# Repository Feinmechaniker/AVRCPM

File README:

Aeternum
CP/M - System auf Basis eines AVR

verwendetets System ZSDOS

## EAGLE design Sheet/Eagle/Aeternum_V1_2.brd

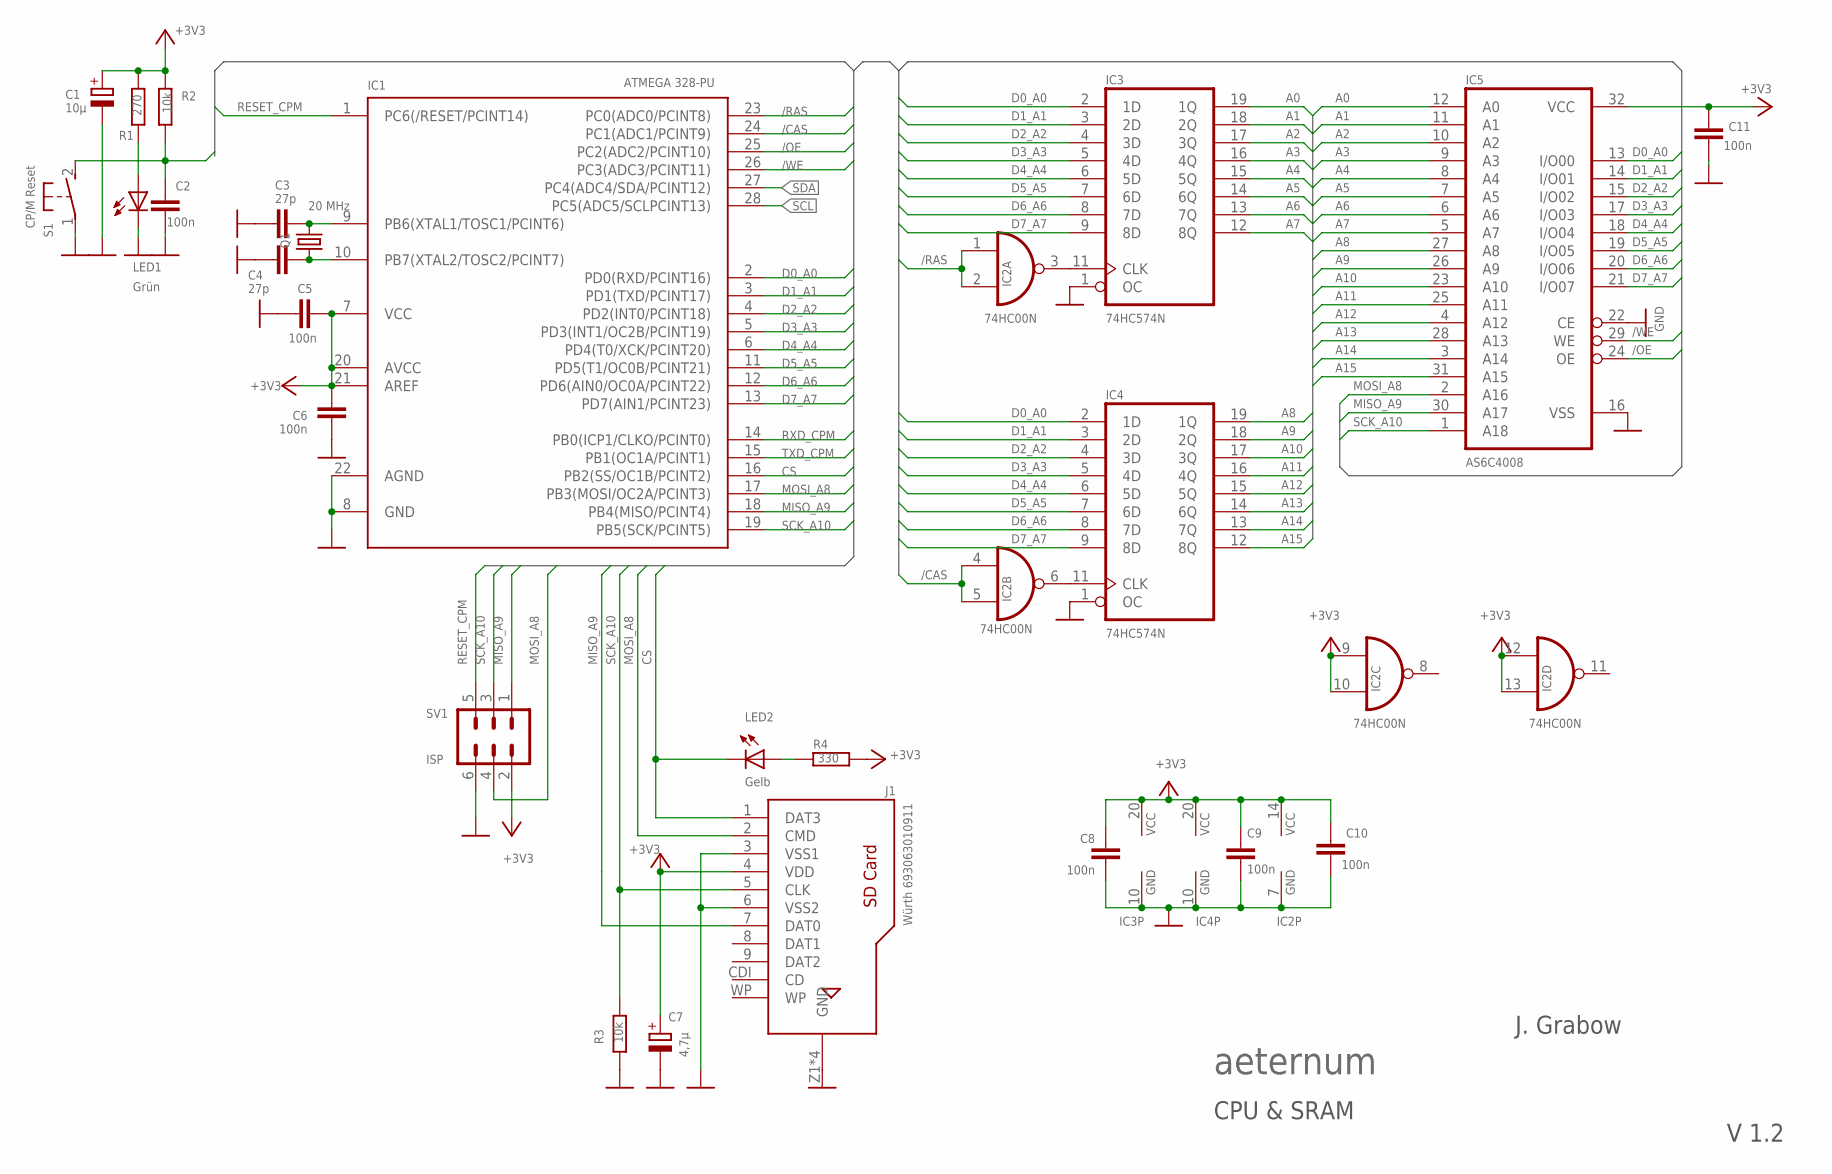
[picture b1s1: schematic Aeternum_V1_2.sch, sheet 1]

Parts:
C1: 10µ; E2-5
C2, C5, C6, C8, C9, C10, C11: 100n; C025-024X044
C3, C4: 27p; C025-024X044
C7: 4,7µ; E2-5
IC1: ATMEGA 328-PU; DIL28-3
IC2: 74HC00N; DIL14
IC3, IC4: 74HC574N; DIL20
IC5: AS6C4008; DIL32
J1: Würth 693063010911; 693063010911
LED1: Grün; CHIPLED_0603
LED2: Gelb; CHIPLED_0603
Q1: 20 MHz; HC49/S
R1: 270; 0204V
R2, R3: 10k; 0204V
R4: 330; 0204V
S1: CP/M Reset; B3F-31XX
SV1: ISP; ML6

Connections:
+3V3: C1.+, C5.1, C6.2, C7.+, C8.1, C9.1, C10.1, C11.1, IC1.7 (VCC), IC1.20 (AVCC), IC1.21 (AREF), IC2.9 (I0), IC2.10 (I1), IC2.12 (I0), IC2.13 (I1), IC2.14 (VCC), IC3.20 (VCC), IC4.20 (VCC), IC5.32 (VCC), J1.4 (VDD), R1.2, R2.1, R4.2, SV1.2; also elsewhere on the board
/CAS: IC1.24 (PC1(ADC1/PCINT9)), IC2.4 (I0), IC2.5 (I1)
/OE: IC1.25 (PC2(ADC2/PCINT10)), IC5.24 (OE)
/RAS: IC1.23 (PC0(ADC0/PCINT8)), IC2.1 (I0), IC2.2 (I1)
/WE: IC1.26 (PC3(ADC3/PCINT11)), IC5.29 (WE)
A0: IC3.19 (1Q), IC5.12 (A0)
A1: IC3.18 (2Q), IC5.11 (A1)
A2: IC3.17 (3Q), IC5.10 (A2)
A3: IC3.16 (4Q), IC5.9 (A3)
A4: IC3.15 (5Q), IC5.8 (A4)
A5: IC3.14 (6Q), IC5.7 (A5)
A6: IC3.13 (7Q), IC5.6 (A6)
A7: IC3.12 (8Q), IC5.5 (A7)
A8: IC4.19 (1Q), IC5.27 (A8)
A9: IC4.18 (2Q), IC5.26 (A9)
A10: IC4.17 (3Q), IC5.23 (A10)
A11: IC4.16 (4Q), IC5.25 (A11)
A12: IC4.15 (5Q), IC5.4 (A12)
A13: IC4.14 (6Q), IC5.28 (A13)
A14: IC4.13 (7Q), IC5.3 (A14)
A15: IC4.12 (8Q), IC5.31 (A15)
CS: IC1.16 (PB2(SS/OC1B/PCINT2)), J1.1 (DAT3), LED2.C
D0_A0: IC1.2 (PD0(RXD/PCINT16)), IC3.2 (1D), IC4.2 (1D), IC5.13 (I/O00)
D1_A1: IC1.3 (PD1(TXD/PCINT17)), IC3.3 (2D), IC4.3 (2D), IC5.14 (I/O01)
D2_A2: IC1.4 (PD2(INT0/PCINT18)), IC3.4 (3D), IC4.4 (3D), IC5.15 (I/O02)
D3_A3: IC1.5 (PD3(INT1/OC2B/PCINT19)), IC3.5 (4D), IC4.5 (4D), IC5.17 (I/O03)
D4_A4: IC1.6 (PD4(T0/XCK/PCINT20)), IC3.6 (5D), IC4.6 (5D), IC5.18 (I/O04)
D5_A5: IC1.11 (PD5(T1/OC0B/PCINT21)), IC3.7 (6D), IC4.7 (6D), IC5.19 (I/O05)
D6_A6: IC1.12 (PD6(AIN0/OC0A/PCINT22)), IC3.8 (7D), IC4.8 (7D), IC5.20 (I/O06)
D7_A7: IC1.13 (PD7(AIN1/PCINT23)), IC3.9 (8D), IC4.9 (8D), IC5.21 (I/O07)
GND: C1.-, C2.1, C3.2, C4.2, C5.2, C6.1, C7.-, C8.2, C9.2, C10.2, C11.2, IC1.8 (GND), IC1.22 (AGND), IC2.7 (GND), IC3.1 (OC), IC3.10 (GND), IC4.1 (OC), IC4.10 (GND), IC5.16 (VSS), IC5.22 (CE), J1.3 (VSS1), J1.6 (VSS2), J1.Z1 (GND), J1.Z2 (GND), J1.Z3 (GND), J1.Z4 (GND), LED1.C, R3.2, S1.1, SV1.6; also elsewhere on the board
MISO_A9: IC1.18 (PB4(MISO/PCINT4)), IC5.30 (A17), J1.7 (DAT0), SV1.1
MOSI_A8: IC1.17 (PB3(MOSI/OC2A/PCINT3)), IC5.2 (A16), J1.2 (CMD), SV1.4
unnamed: C4.1, IC1.10 (PB7(XTAL2/TOSC2/PCINT7)), Q1.1
unnamed: IC2.3 (O), IC3.11 (CLK)
unnamed: LED1.A, R1.1
unnamed: LED2.A, R4.1
unnamed: C3.1, IC1.9 (PB6(XTAL1/TOSC1/PCINT6)), Q1.2
unnamed: IC2.6 (O), IC4.11 (CLK)
RESET_CPM: C2.2, IC1.1 (PC6(/RESET/PCINT14)), R2.2, S1.2 (S), SV1.5; also elsewhere on the board
RXD_CPM: IC1.14 (PB0(ICP1/CLKO/PCINT0)); also elsewhere on the board
SCK_A10: IC1.19 (PB5(SCK/PCINT5)), IC5.1 (A18), J1.5 (CLK), R3.1, SV1.3
SCL: IC1.28 (PC5(ADC5/SCLPCINT13)); also elsewhere on the board
SDA: IC1.27 (PC4(ADC4/SDA/PCINT12)); also elsewhere on the board
TXD_CPM: IC1.15 (PB1(OC1A/PCINT1)); also elsewhere on the board

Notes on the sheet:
aeternum
V 1.2
J. Grabow
CPU & SRAM

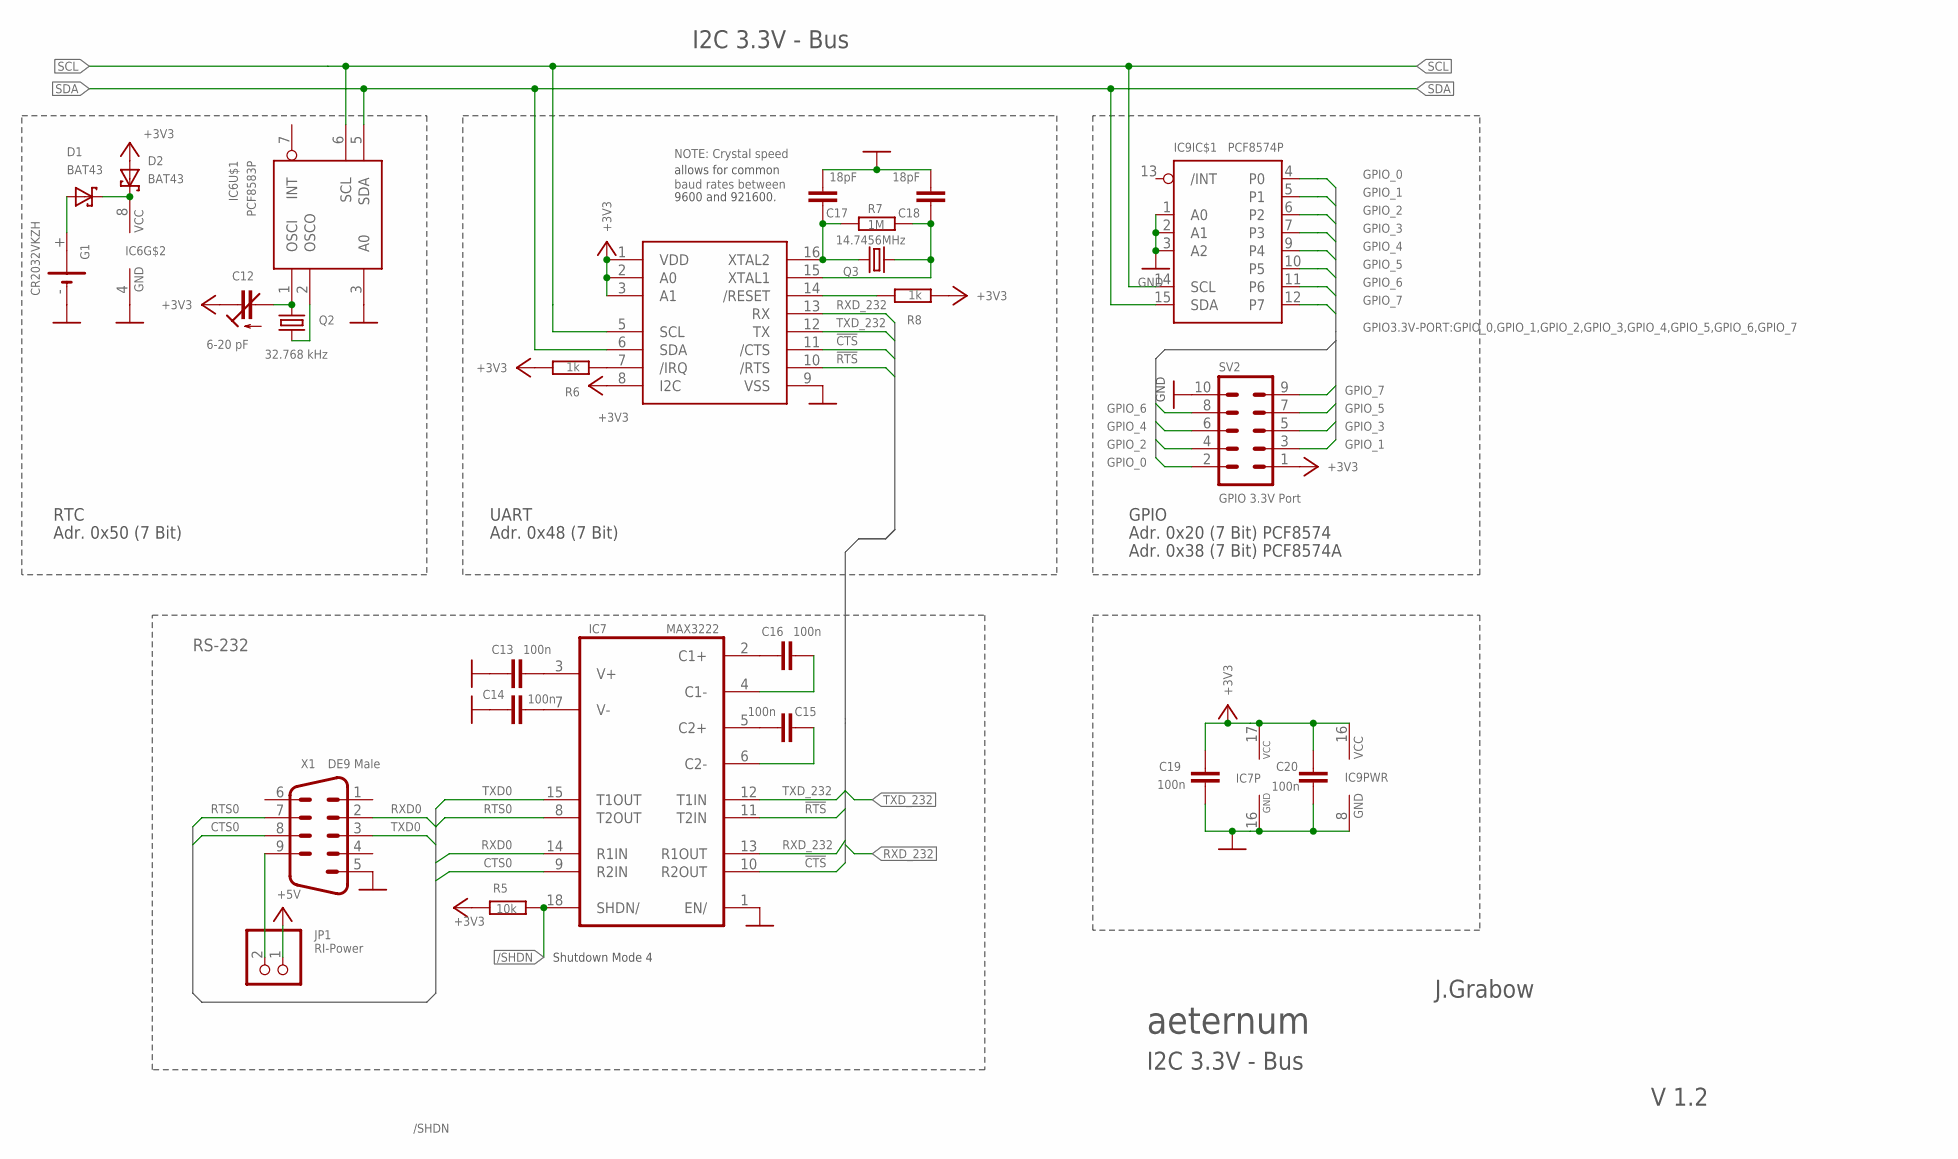
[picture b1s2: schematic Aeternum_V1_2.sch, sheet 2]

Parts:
C12: 6-20 pF; CTRIMTZ03
C13, C14, C15, C16, C19, C20: 100n; C025-024X044
C17, C18: 18pF; 0603-CAP
D1, D2: BAT43; E2LINE
G1: CR2032VKZH; KZH20PCB-V
IC6: PCF8583P; DIL08
IC7: MAX3222; DIL18
IC8: SC16IS740; RICKK2_SC16IS740
IC9: PCF8574P; DIL16
JP1: RI-Power; 1X02
Q2: 32.768 kHz; TC26H
Q3: 14.7456MHz; CRYSTAL-SMD-5X3
R5: 10k; 0204V
R6, R8: 1k; R0805
R7: 1M; R0805
SV2: GPIO 3.3V Port; ML10L
X1: DE9 Male; M09HP

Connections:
!CTS: IC7.10 (R2OUT), IC8.11 (/CTS)
!RTS: IC7.11 (T2IN), IC8.10 (/RTS)
+3V3: C12.1 (E), C19.2, C20.2, D2.2 (A), IC7.17 (VCC), IC8.1 (VDD), IC8.2 (A0), IC8.3 (A1), IC8.8 (I2C), IC9.16 (VCC), R5.2, R6.2, R8.1, SV2.1; also elsewhere on the board
+5V: JP1.1; also elsewhere on the board
/SHDN: IC7.18 (SHDN/), R5.1; also elsewhere on the board
CTS0: IC7.9 (R2IN), X1.8
GND: C13.2, C14.2, C17.2, C18.2, C19.1, C20.1, G1.-, IC6.3 (A0), IC6.4 (GND), IC7.1 (EN/), IC7.16 (GND), IC8.9 (VSS), IC9.1 (A0), IC9.2 (A1), IC9.3 (A2), IC9.8 (GND), SV2.10, X1.5; also elsewhere on the board
GPIO_0: IC9.4 (P0), SV2.2
GPIO_1: IC9.5 (P1), SV2.3
GPIO_2: IC9.6 (P2), SV2.4
GPIO_3: IC9.7 (P3), SV2.5
GPIO_4: IC9.9 (P4), SV2.6
GPIO_5: IC9.10 (P5), SV2.7
GPIO_6: IC9.11 (P6), SV2.8
GPIO_7: IC9.12 (P7), SV2.9
unnamed: C12.2 (A), IC6.1 (OSCI), Q2.1
unnamed: IC6.2 (OSCO), Q2.2
unnamed: C17.1, IC8.16 (XTAL2), Q3.3 (2), R7.1
unnamed: C16.2, IC7.2 (C1+)
unnamed: JP1.2, X1.9
unnamed: C15.1, IC7.5 (C2+)
unnamed: C14.1, IC7.7 (V-)
unnamed: C16.1, IC7.4 (C1-)
unnamed: C15.2, IC7.6 (C2-)
unnamed: C13.1, IC7.3 (V+)
unnamed: D1.1 (K), D2.1 (K), IC6.8 (VCC)
unnamed: D1.2 (A), G1.+
unnamed: C18.1, IC8.15 (XTAL1), Q3.1, R7.2
unnamed: IC8.14 (/RESET), R8.2
unnamed: IC8.7 (/IRQ), R6.1
RTS0: IC7.8 (T2OUT), X1.7
RXD0: IC7.14 (R1IN), X1.2
RXD_232: IC7.13 (R1OUT), IC8.13 (RX); also elsewhere on the board
SCL: IC6.6 (SCL), IC8.5 (SCL), IC9.14 (SCL); also elsewhere on the board
SDA: IC6.5 (SDA), IC8.6 (SDA), IC9.15 (SDA); also elsewhere on the board
TXD0: IC7.15 (T1OUT), X1.3
TXD_232: IC7.12 (T1IN), IC8.12 (TX); also elsewhere on the board

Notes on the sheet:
Adr. 0x50 (7 Bit)
RTC
NOTE: Crystal speed
baud rates between
UART
Adr. 0x48 (7 Bit)
allows for common
9600 and 921600.
GPIO
Adr. 0x20 (7 Bit) PCF8574
J.Grabow
V 1.2
I2C 3.3V - Bus
aeternum
RS-232
Shutdown Mode 4
Adr. 0x38 (7 Bit) PCF8574A

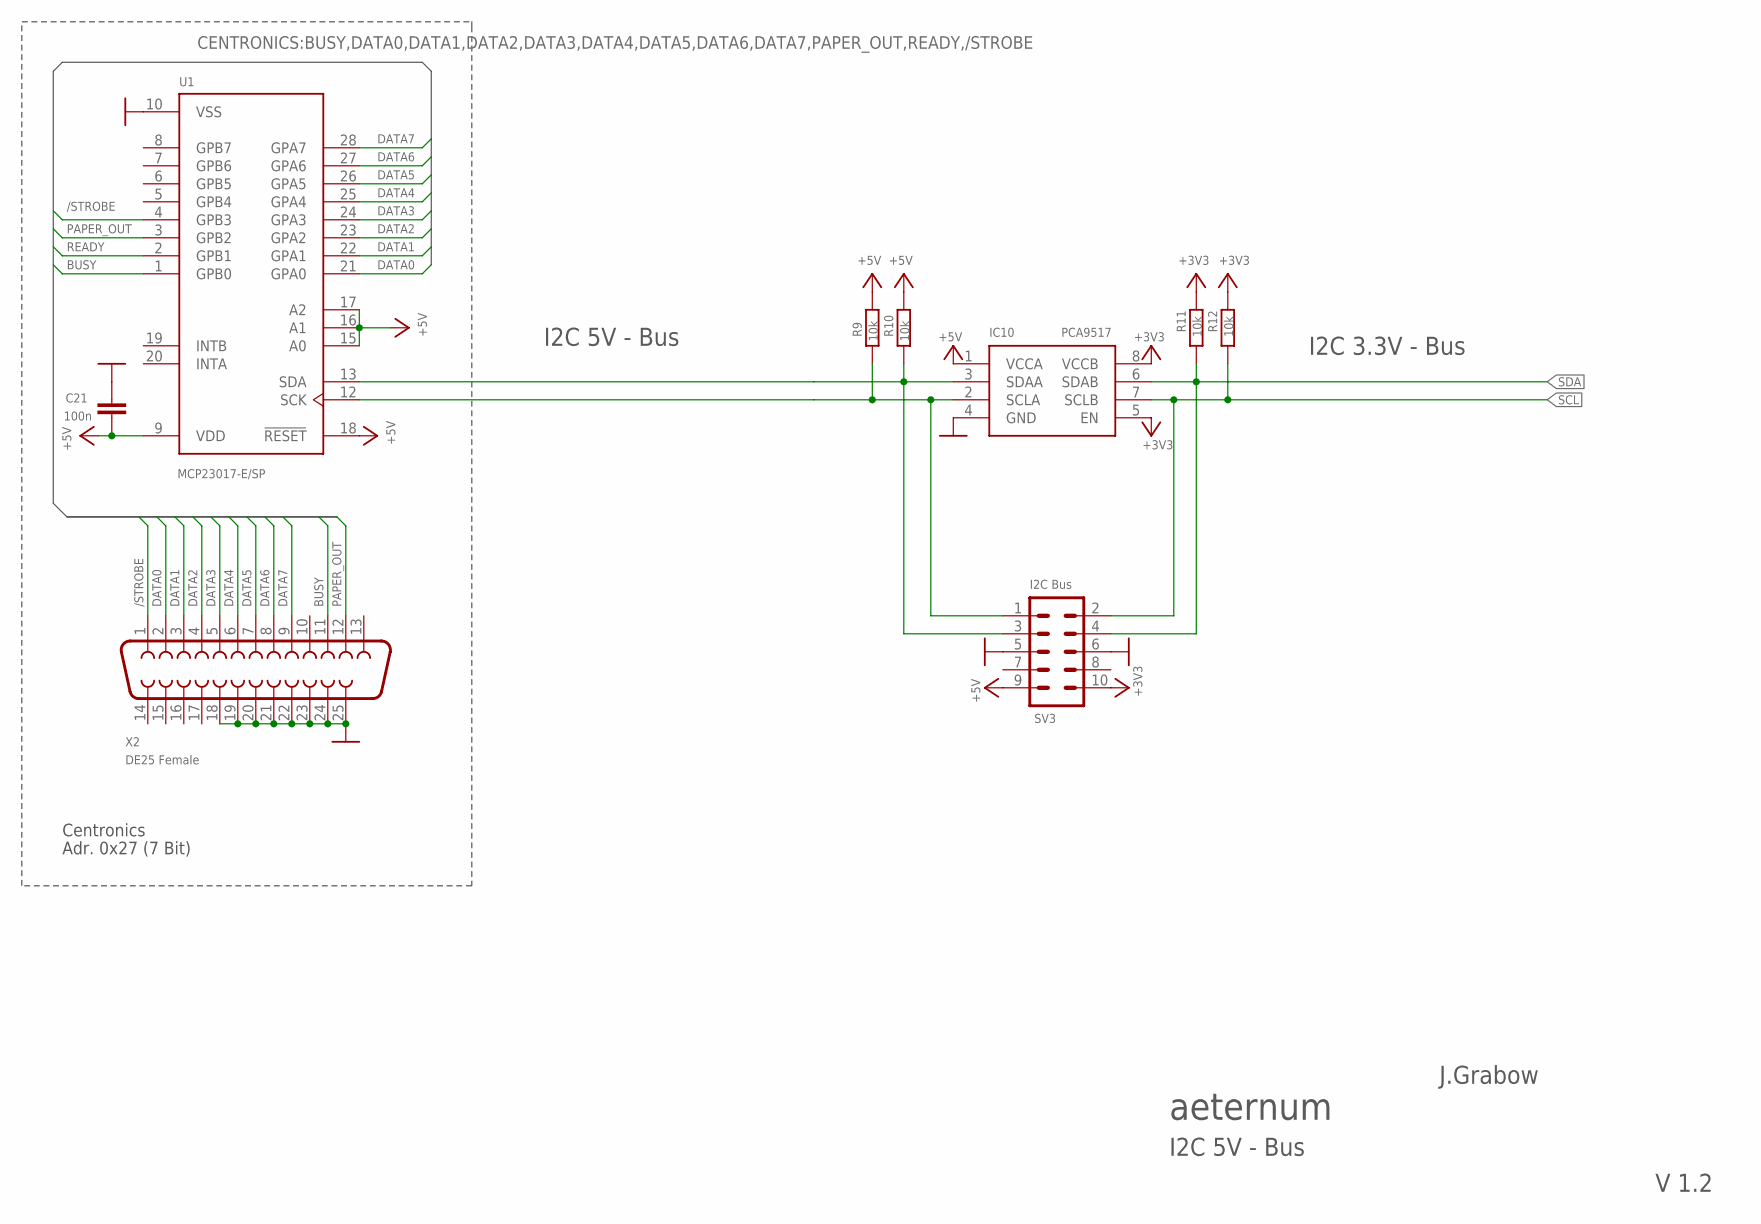
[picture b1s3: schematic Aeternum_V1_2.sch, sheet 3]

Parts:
C21: 100n; C025-024X044
IC10: PCA9517; SO-08
R9, R10, R11, R12: 10k; 0207/2V
SV3: I2C Bus; ML10L
U1: MCP23017-E/SP; DIP793W45P254L3556H508Q28
X2: DE25 Female; F25H

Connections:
+3V3: IC10.5 (EN), IC10.8 (VCCB), R11.2, R12.2, SV3.10; also elsewhere on the board
+5V: C21.1, IC10.1 (VCCA), R9.2, R10.2, SV3.9, U1.9 (VDD), U1.15 (A0), U1.16 (A1), U1.17 (A2), U1.18 (!RESET); also elsewhere on the board
/STROBE: U1.4 (GPB3), X2.1
BUSY: U1.1 (GPB0), X2.11
DATA0: U1.21 (GPA0), X2.2
DATA1: U1.22 (GPA1), X2.3
DATA2: U1.23 (GPA2), X2.4
DATA3: U1.24 (GPA3), X2.5
DATA4: U1.25 (GPA4), X2.6
DATA5: U1.26 (GPA5), X2.7
DATA6: U1.27 (GPA6), X2.8
DATA7: U1.28 (GPA7), X2.9
GND: C21.2, IC10.4 (GND), SV3.5, SV3.6, U1.10 (VSS), X2.18, X2.19, X2.20, X2.21, X2.22, X2.23, X2.24, X2.25; also elsewhere on the board
PAPER_OUT: U1.3 (GPB2), X2.12
READY: U1.2 (GPB1)
SCL: IC10.7 (SCLB), R12.1, SV3.2; also elsewhere on the board
SCLA: IC10.2 (SCLA), R9.1, SV3.1, U1.12 (SCK)
SDA: IC10.6 (SDAB), R11.1, SV3.4; also elsewhere on the board
SDAA: IC10.3 (SDAA), R10.1, SV3.3, U1.13 (SDA)

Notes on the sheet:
I2C 5V - Bus
aeternum
J.Grabow
V 1.2
I2C 3.3V - Bus
Adr. 0x27 (7 Bit)
Centronics

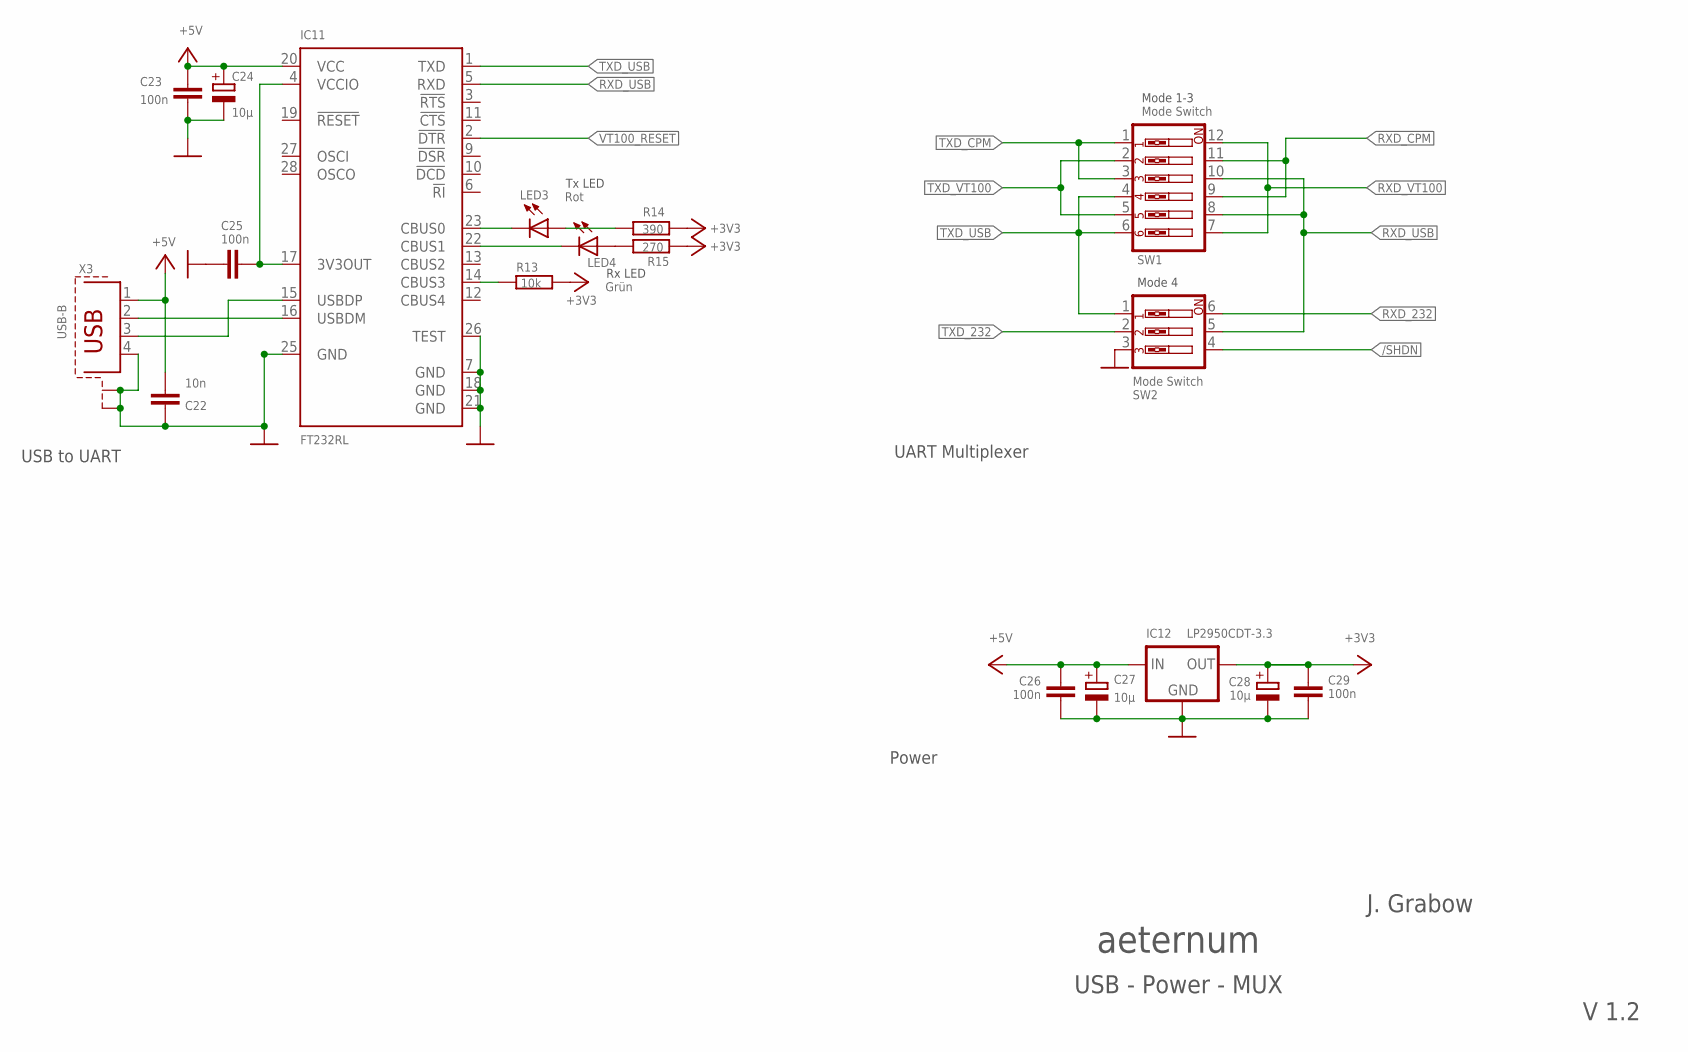
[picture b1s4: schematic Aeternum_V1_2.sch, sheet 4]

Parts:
C22: 10n; C025-024X044
C23, C25, C26, C29: 100n; C025-024X044
C24, C27, C28: 10µ; E2-5
IC11: FT232RL; SSOP28
IC12: LP2950CDT-3.3; DPACK
LED3: Rot; CHIPLED_0603
LED4: Grün; CHIPLED_0603
R13: 10k; 0204V
R14: 390; 0204V
R15: 270; 0204V
SW1: Mode Switch; EDG-06
SW2: Mode Switch; EDG-03
X3: USB-B; PN61729-S

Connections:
+3V3: C28.+, C29.2, IC12.3 (OUT), R13.2, R14.2, R15.2; also elsewhere on the board
+5V: C22.2, C23.2, C24.+, C26.2, C27.+, IC11.20 (VCC), IC12.1 (IN), X3.1; also elsewhere on the board
/SHDN: SW2.4; also elsewhere on the board
GND: C22.1, C23.1, C24.-, C25.1, C26.1, C27.-, C28.-, C29.1, IC11.7 (GND), IC11.18 (GND), IC11.21 (GND), IC11.25 (GND), IC11.26 (TEST), IC12.4 (GND), SW2.3, X3.4, X3.S1, X3.S2; also elsewhere on the board
unnamed: IC11.16 (USBDM), X3.2
unnamed: IC11.15 (USBDP), X3.3
unnamed: IC11.14 (CBUS3), R13.1
unnamed: C25.2, IC11.4 (VCCIO), IC11.17 (3V3OUT)
unnamed: IC11.23 (CBUS0), LED3.C
unnamed: IC11.22 (CBUS1), LED4.C
unnamed: LED4.A, R15.1
unnamed: LED3.A, R14.1
RXD_232: SW2.6; also elsewhere on the board
RXD_CPM: SW1.9, SW1.11; also elsewhere on the board
RXD_USB: IC11.5 (RXD), SW1.8, SW1.10, SW2.5
RXD_VT100: SW1.7, SW1.12; also elsewhere on the board
TXD_232: SW2.2; also elsewhere on the board
TXD_CPM: SW1.1, SW1.3; also elsewhere on the board
TXD_USB: IC11.1 (TXD), SW1.4, SW1.6, SW2.1
TXD_VT100: SW1.2, SW1.5; also elsewhere on the board
VT100_RESET: IC11.2 (!DTR); also elsewhere on the board

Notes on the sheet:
Mode 1-3
Mode 4
USB to UART
UART Multiplexer
Power
USB - Power - MUX
aeternum
J. Grabow
V 1.2
Tx LED
Rx LED

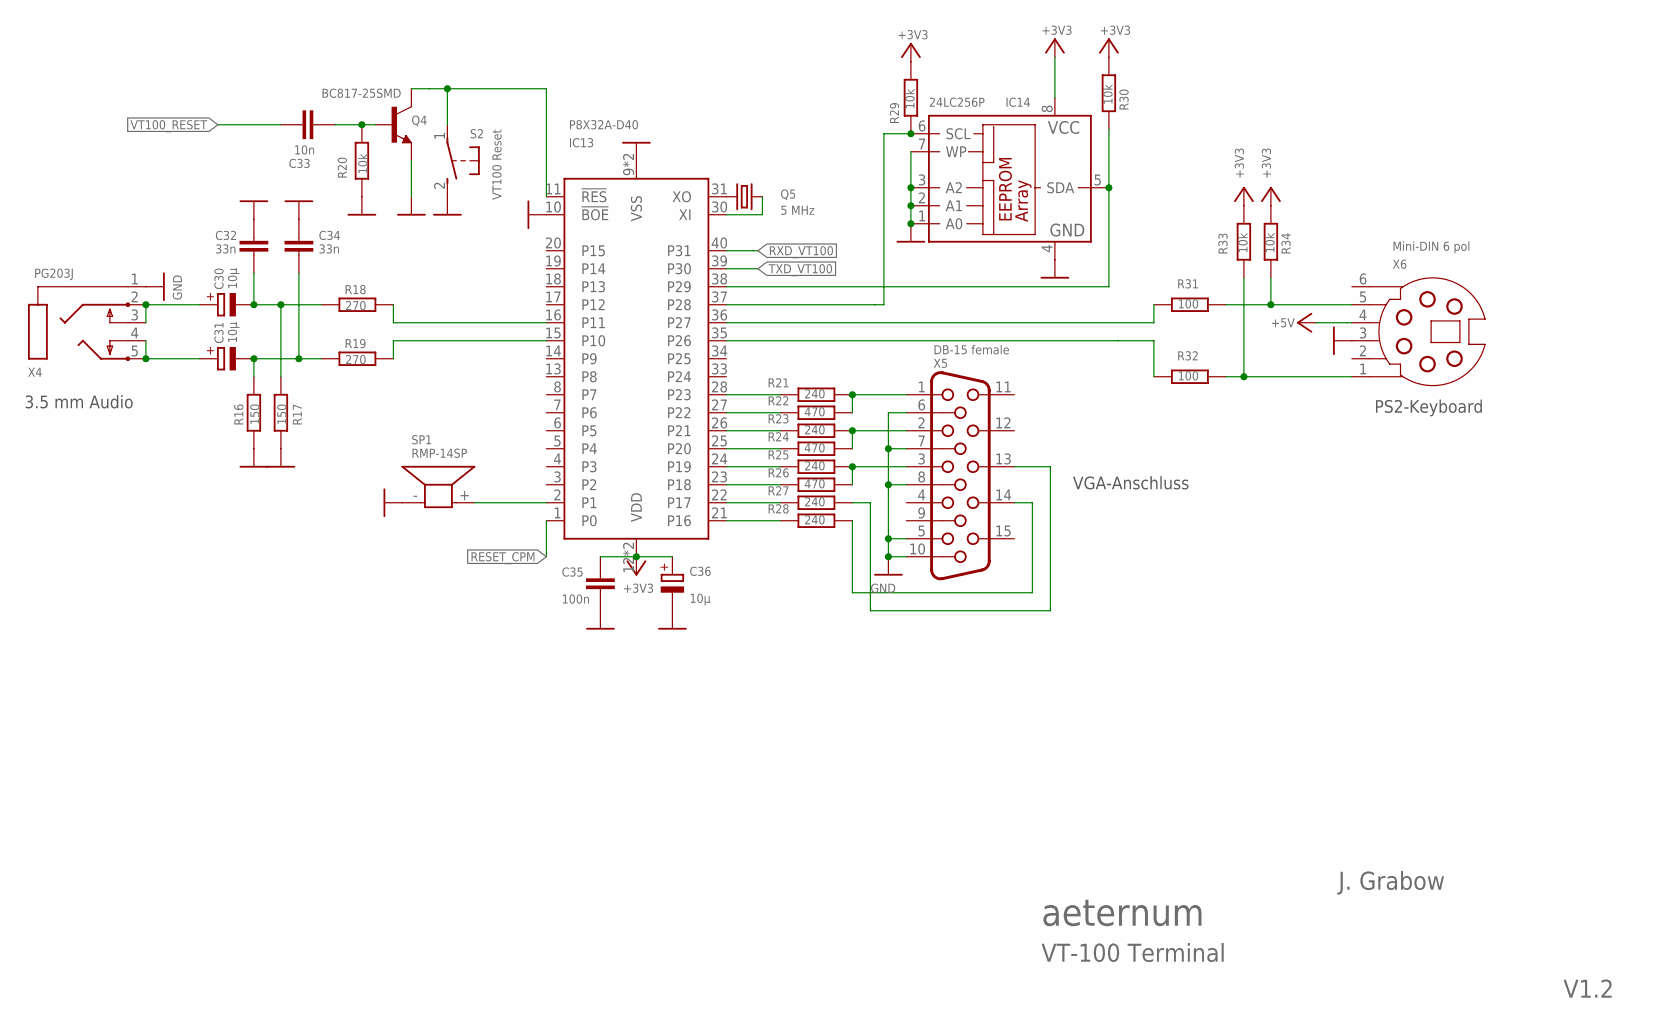
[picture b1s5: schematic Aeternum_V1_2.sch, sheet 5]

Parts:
C30, C31: 10µ; E2,5-5
C32, C34: 33n; C025-024X044
C33: 10n; C025-024X044
C35: 100n; C025-024X044
C36: 10µ; E2,5-6E
IC13: P8X32A-D40; DIL40
IC14: 24LC256P; DIL8
Q4: BC817-25SMD; SOT23-BEC
Q5: 5 MHz; HC49/S
R16, R17: 150; 0204V
R18, R19: 270; 0204V
R20, R33, R34: 10k; 0204V
R21, R23, R25, R27, R28: 240; 0204V
R22, R24, R26: 470; 0204V
R29, R30: 10k; 0204/7
R31, R32: 100; 0204V
S2: VT100 Reset; B3F-31XX
SP1: RMP-14SP; KSS1201
X4: PG203J
X5: DB-15 female; HDF15H
X6: Mini-DIN 6 pol; SSV-BC06

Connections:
+3V3: C35.2, C36.+, IC13.12 (VDD), IC13.32 (VDD), IC14.8 (VCC), R29.1, R30.1, R33.1, R34.1; also elsewhere on the board
+5V: X6.4; also elsewhere on the board
GND: C32.2, C34.2, C35.1, C36.-, IC13.9 (VSS), IC13.10 (!BOE), IC13.29 (VSS), IC14.1 (A0), IC14.2 (A1), IC14.3 (A2), IC14.4 (GND), IC14.7 (WP), Q4.E, R16.2, R17.2, R20.1, S2.2 (S), SP1.- (2), X4.1, X5.5, X5.6, X5.7, X5.8, X5.10, X6.3; also elsewhere on the board
unnamed: IC13.30 (XI), Q5.1
unnamed: R21.1, R22.1, X5.1
unnamed: IC13.28 (P23), R21.2
unnamed: IC13.27 (P22), R22.2
unnamed: R23.1, R24.1, X5.2
unnamed: IC13.26 (P21), R23.2
unnamed: IC13.25 (P20), R24.2
unnamed: R25.1, R26.1, X5.3
unnamed: IC13.24 (P19), R25.2
unnamed: IC13.23 (P18), R26.2
unnamed: IC13.22 (P17), R27.2
unnamed: IC13.21 (P16), R28.2
unnamed: R27.1, X5.13
unnamed: R28.1, X5.14
unnamed: R32.1, R33.2, X6.1
unnamed: R31.1, R34.2, X6.5
unnamed: IC13.31 (XO), Q5.2
unnamed: IC13.2 (P1), SP1.+ (1)
unnamed: C33.2, Q4.B, R20.2
unnamed: IC13.37 (P28), IC14.6 (SCL), R29.2
unnamed: IC13.38 (P29), IC14.5 (SDA), R30.2
unnamed: C31.-, C34.1, R16.1, R19.2
unnamed: C30.-, C32.1, R17.1, R18.2
unnamed: C30.+, X4.2, X4.3
unnamed: C31.+, X4.4, X4.5
P10: IC13.16 (P11), R18.1
P11: IC13.15 (P10), R19.1
P26: IC13.35 (P26), R32.2
P27: IC13.36 (P27), R31.2
PROP_RESET: IC13.11 (!RES), Q4.C, S2.1
RESET_CPM: IC13.1 (P0); also elsewhere on the board
RXD_VT100: IC13.40 (P31); also elsewhere on the board
TXD_VT100: IC13.39 (P30); also elsewhere on the board
VT100_RESET: C33.1; also elsewhere on the board

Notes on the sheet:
aeternum
J. Grabow
VT-100 Terminal
V1.2
PS2-Keyboard
VGA-Anschluss
3.5 mm Audio

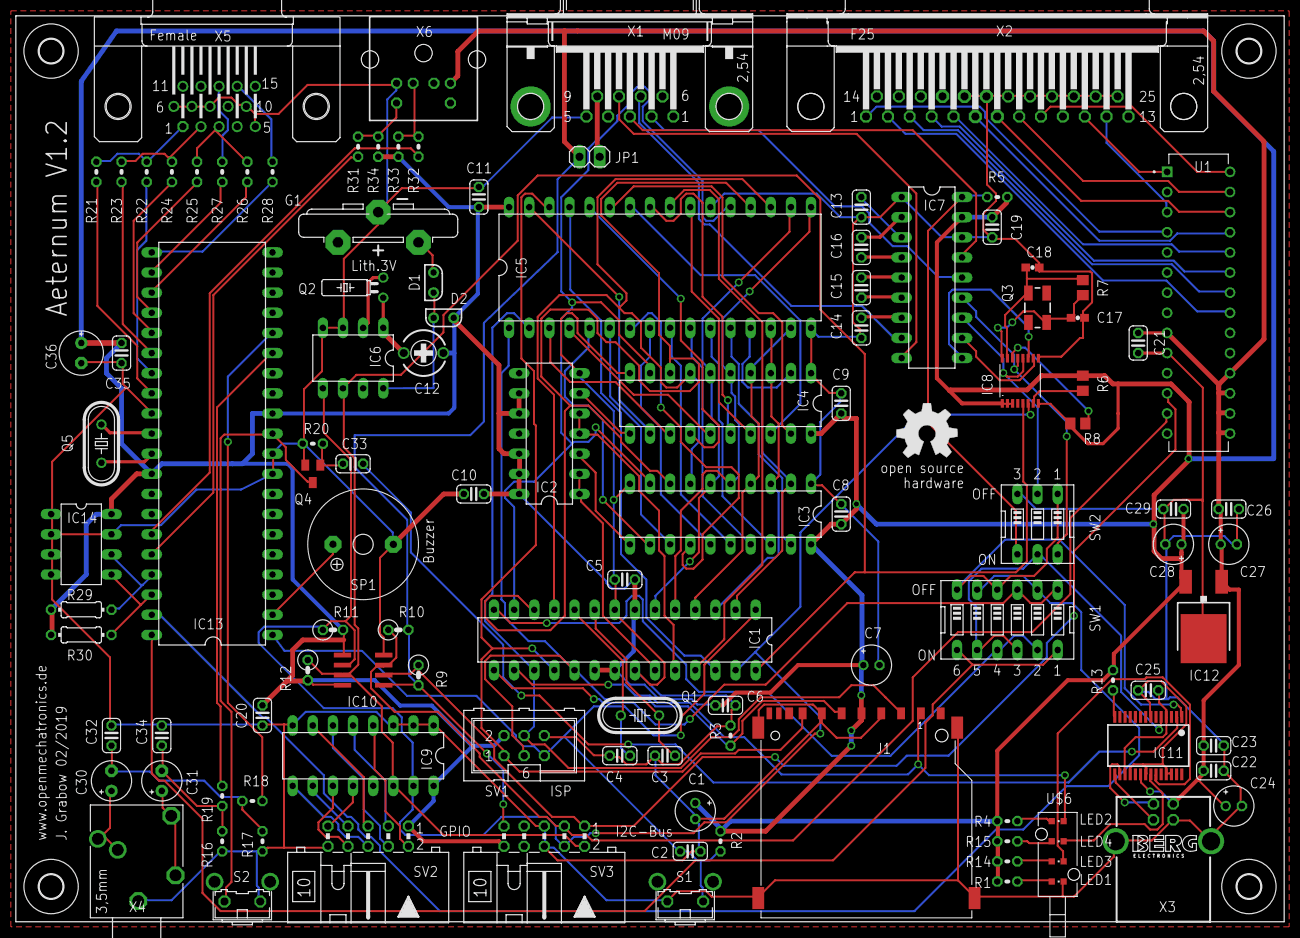
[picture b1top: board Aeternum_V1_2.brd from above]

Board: 2 copper layers, 160.0 x 114.3 mm, 119 parts (0 on the bottom side), 134 nets.

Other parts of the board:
U$1, U$2, U$3, U$4: 3,0
U$6: OPTO_THT_LWL_MENTOR_1296_1004
U$7: OSHW_8MM

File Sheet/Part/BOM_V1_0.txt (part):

Stückliste exportiert aus B:/Projekte/02 AVR CPM/Sheet/Aeternum_V1.sch am 07.03.2019 10:07

Part Value              Device           Package                   Description                                                                                                   
C1   10µ                CPOL-EUE2-5      E2-5                      POLARIZED CAPACITOR, European symbol                                                                          
C2   100n               C-EU025-024X044  C025-024X044              CAPACITOR, European symbol                                                                                    
C3   27p                C-EU025-024X044  C025-024X044              CAPACITOR, European symbol                                                                                    
C4   27p                C-EU025-024X044  C025-024X044              CAPACITOR, European symbol                                                                                    
C5   100n               C-EU025-024X044  C025-024X044              CAPACITOR, European symbol                                                                                    
C6   100n               C-EU025-024X044  C025-024X044              CAPACITOR, European symbol                                                                                    
C7   4,7µ               CPOL-EUE2-5      E2-5                      POLARIZED CAPACITOR, European symbol                                                                          
C8   100n               C-EU025-024X044  C025-024X044              CAPACITOR, European symbol                                                                                    
C9   100n               C-EU025-024X044  C025-024X044              CAPACITOR, European symbol                                                                                    
C10  100n               C-EU025-024X044  C025-024X044              CAPACITOR, European symbol                                                                                    
C11  100n               C-EU025-024X044  C025-024X044              CAPACITOR, European symbol                                                                                    
C12  6-20 pF            C-TRIMMTZ03      CTRIMTZ03                 Trimm capacitor                                                                                               
C13  100n               C-EU025-024X044  C025-024X044              CAPACITOR, European symbol                                                                                    
C14  100n               C-EU025-024X044  C025-024X044              CAPACITOR, European symbol                                                                                    
C15  100n               C-EU025-024X044  C025-024X044              CAPACITOR, European symbol                                                                                    
C16  100n               C-EU025-024X044  C025-024X044              CAPACITOR, European symbol                                                                                    
C17  18pF               CAP0402-CAP      0402-CAP                  Capacitor                                                                                                     
C18  18pF               CAP0402-CAP      0402-CAP                  Capacitor                                                                                                     
C19  100n               C-EU025-024X044  C025-024X044              CAPACITOR, European symbol                                                                                    
C20  100n               C-EU025-024X044  C025-024X044              CAPACITOR, European symbol                                                                                    
C21  100n               C-EUC0805        C0805                     CAPACITOR, European symbol                                                                                    
C22  10n                C-EU025-024X044  C025-024X044              CAPACITOR, European symbol                                                                                    
C23  100n               C-EU025-024X044  C025-024X044              CAPACITOR, European symbol                                                                                    
C24  10µ                CPOL-EUE2-5      E2-5                      POLARIZED CAPACITOR, European symbol                                                                          
C25  100n               C-EU025-024X044  C025-024X044              CAPACITOR, European symbol                                                                                    
C26  100n               C-EU025-024X044  C025-024X044              CAPACITOR, European symbol                                                                                    
C27  10µ                CPOL-EUE2-5      E2-5                      POLARIZED CAPACITOR, European symbol                                                                          
C28  10µ                CPOL-EUE2-5      E2-5                      POLARIZED CAPACITOR, European symbol                                                                          
C29  100n               C-EU025-024X044  C025-024X044              CAPACITOR, European symbol                                                                                    
C30  10µ                CPOL-EUE2.5-5    E2,5-5                    POLARIZED CAPACITOR, European symbol                                                                          
C31  10µ                CPOL-EUE2.5-5    E2,5-5                    POLARIZED CAPACITOR, European symbol                                                                          
C32  33n                C-EU025-024X044  C025-024X044              CAPACITOR, European symbol                                                                                    
C33  10n                C-EU025-024X044  C025-024X044              CAPACITOR, European symbol                                                                                    
C34  33n                C-EU025-024X044  C025-024X044              CAPACITOR, European symbol                                                                                    
C35  100n               C-EU025-024X044  C025-024X044              CAPACITOR, European symbol                                                                                    
C36  10µ                CPOL-EUE2,5-6E   E2,5-6E                   POLARIZED CAPACITOR, European symbol                                                                          
D1   BAT43              DS_E2L           E2LINE                    SHOTTKY DIODE                                                                                                 
D2   BAT43              DS_E2L           E2LINE                    SHOTTKY DIODE                                                                                                 
G1   CR2032VKZH         CR2032VKZH       KZH20PCB-V                LI BATTERY Varta                                                                                              
IC1  ATMEGA 328-PU      MEGA48/88/168-PU DIL28-3                                                                                                                                 
IC2  74HC00N            74HC00N          DIL14                     Quad 2-input NAND gate                                                                                        
IC3  74HC574N           74HC574N         DIL20                     8-bit D type FLIP FLOP bus driver                                                                             
IC4  74HC574N           74HC574N         DIL20                     8-bit D type FLIP FLOP bus driver                                                                             
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
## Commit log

2019-02-21 AVR Code
2019-02-21 Readme eingefügt
2019-02-21 ZSDOS (CP/M 2.2) erstellen
2019-02-21 README
2019-03-01 VT100 Code
2019-03-01 System Files
2019-03-02 new EEPROM basic adress
2019-03-02 new EEPROM adress
2019-03-04 new Image
2019-03-04 new build
2019-03-04 new BIOS (CP/M 2.2)
2019-03-05 new version
2019-03-05 new VT100 Version
2019-03-06 CP/M Modem Tools
2019-03-06 CP/M Tools
2019-03-06 Bugfix
2019-03-07 Partlist
2019-03-07 Sheet & PCB
2019-03-07 EAGLE data
2019-03-07 Parts (Reichelt)
2019-03-07 overview
2019-03-07 case part 1
2019-03-07 case part 2
2019-03-07 picture of case
2019-03-07 in revision
2019-03-07 Errata V1.0
2019-03-08 added connectors
2019-03-15 new diameter for keybord connector
2019-03-27 Doku erweitert
2019-04-01 new chapter, serial port
2019-04-14 Errate and Doku
2019-04-14 Version 1.3
2019-08-01 AVR Project for Atmel Studio 7

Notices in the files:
parts and their libraries:
InputOutputIO: Copyright: Würth Elektronik
